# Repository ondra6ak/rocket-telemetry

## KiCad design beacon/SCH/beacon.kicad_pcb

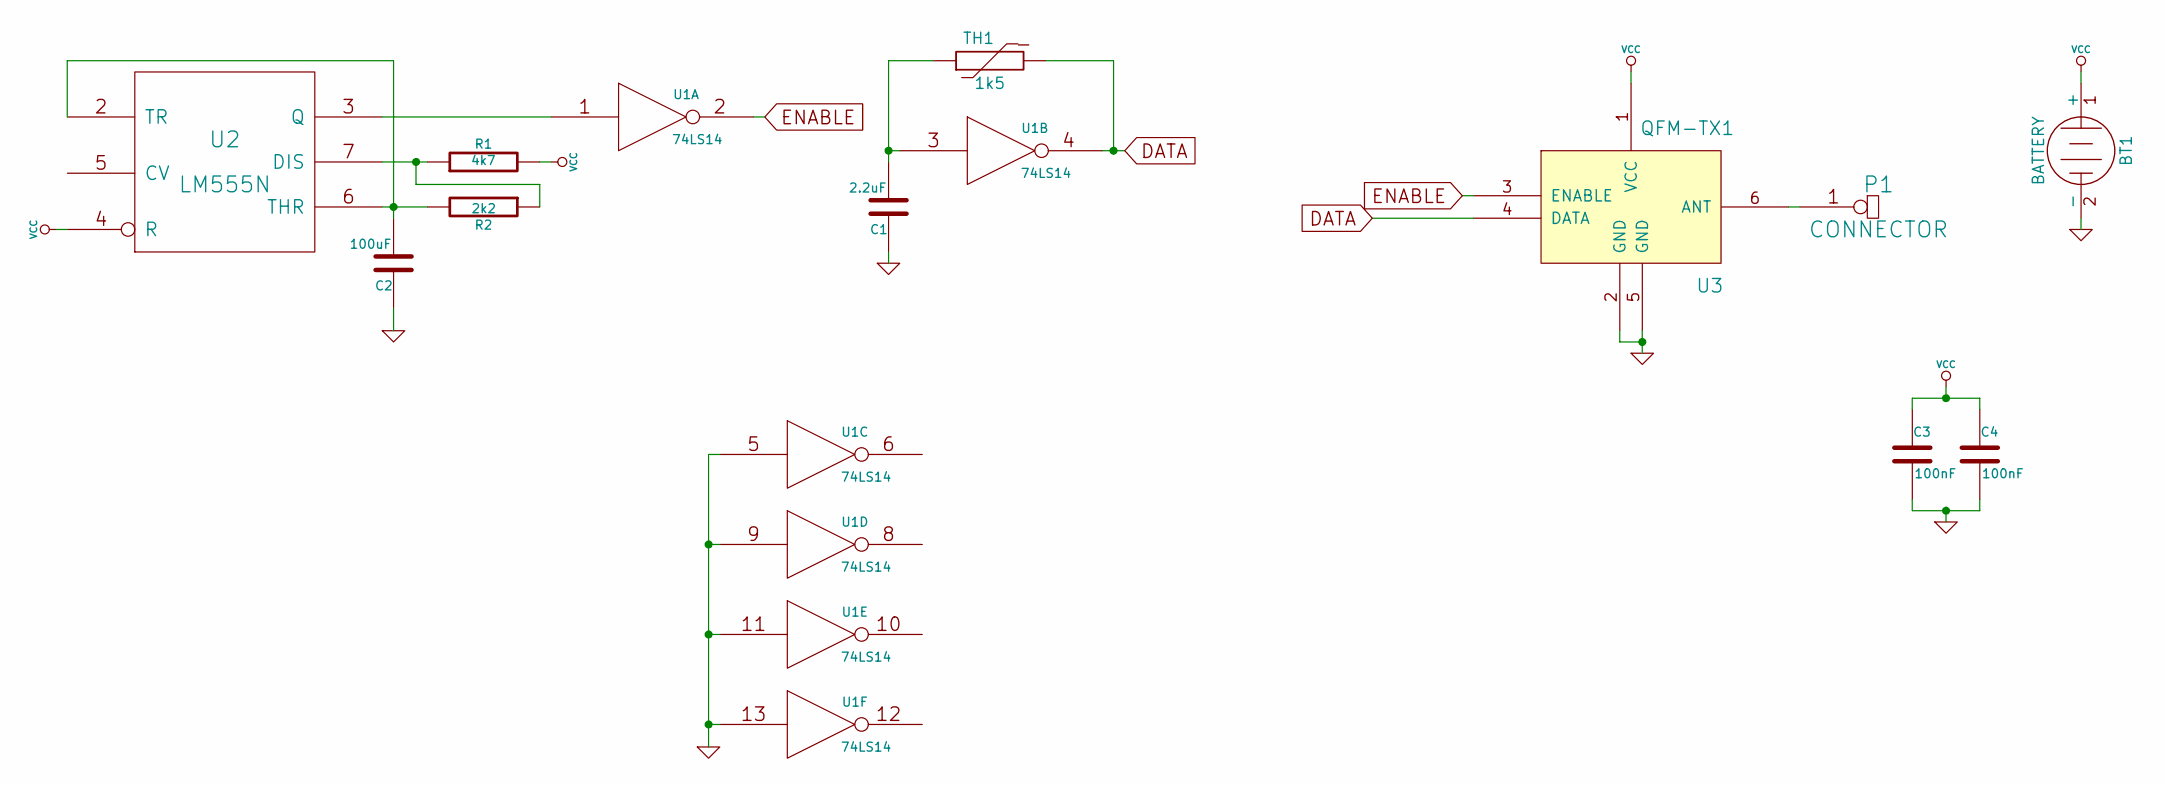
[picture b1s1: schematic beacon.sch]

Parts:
BT1: BATTERY; Coin_Cell_Holder_CH25-2032LF
C1: 2.2uF; C_0805
C2: 100uF; C_0805
C3, C4: 100nF; C_0805
P1: CONNECTOR; Pin_Header_Straight_1x01
R1: 4k7; R_0805_HandSoldering
R2: 2k2; R_0805_HandSoldering
TH1: 1k5; Capacitor7x3-5RM5_RevB
U1: 74LS14; SOIC-14_W
U2: LM555N; SOIC-8-W
U3: QFM-TX1

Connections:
DATA: TH1.2, U1.4, U3.4 (DATA)
ENABLE: U1.2, U3.3 (ENABLE)
GND: BT1.2 (-), C1.1, C2.1, C3.2, C4.2, U1.5, U1.7 (GND), U1.9, U1.11, U1.13, U2.1 (GND), U3.2 (GND), U3.5 (GND)
unnamed: C1.2, TH1.1, U1.3
unnamed: C2.2, R2.2, U2.2 (TR), U2.6 (THR)
unnamed: P1.1, U3.6 (ANT)
unnamed: R1.1, R2.1, U2.7 (DIS)
unnamed: U1.1, U2.3 (Q)
VCC: BT1.1 (+), C3.1, C4.1, R1.2, U1.14 (VCC), U2.4 (R), U2.8 (VCC), U3.1 (VCC)

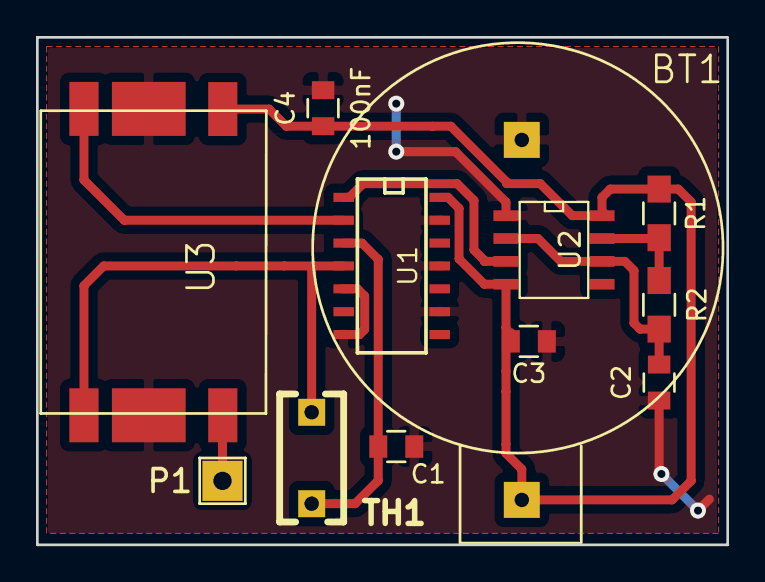
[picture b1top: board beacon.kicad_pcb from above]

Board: 2 copper layers, 38.4 x 28.2 mm, 12 parts (0 on the bottom side), 9 nets.

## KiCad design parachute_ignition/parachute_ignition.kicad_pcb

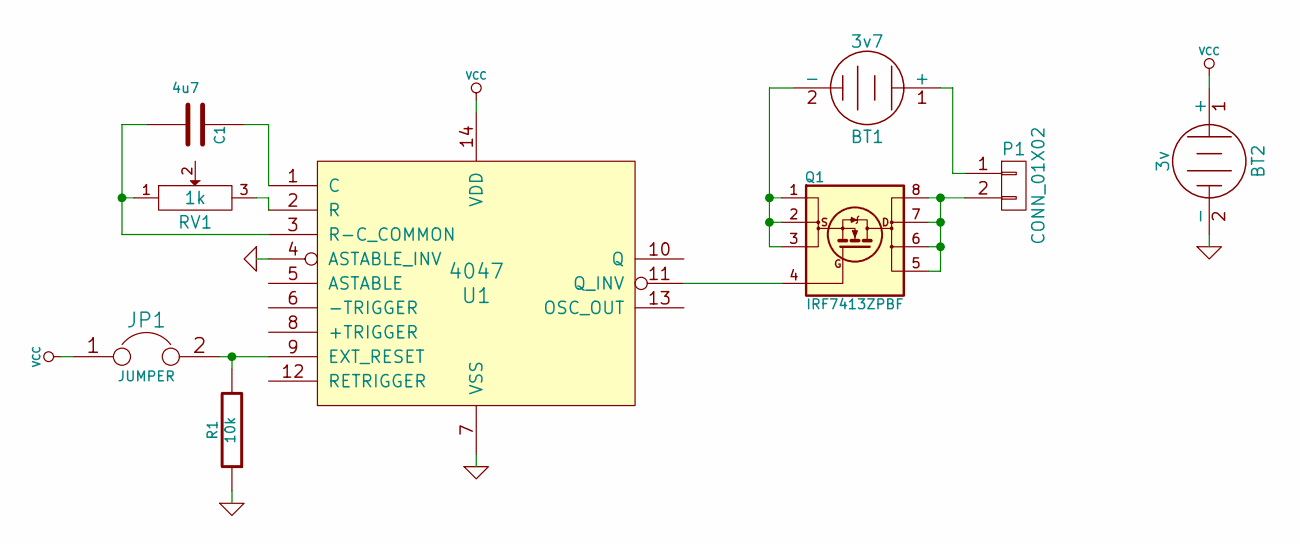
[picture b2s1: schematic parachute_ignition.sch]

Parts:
BT1: 3v7; Pin_Header_Straight_1x02
BT2: 3v; Coin_Cell_Holder_CH25-2032LF
C1: 4u7; C_0805
JP1: JUMPER; Pin_Header_Straight_1x02
P1: CONN_01X02; Pin_Header_Straight_1x02
Q1: IRF7413ZPBF; SOIC-8-W
R1: 10k; R_0805_HandSoldering
RV1: 1k; Koa_Trimmer_Smd_C
U1: 4047; SOIC-14_W

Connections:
GND: BT2.2 (-), R1.1, U1.4 (ASTABLE_INV), U1.7 (VSS)
unnamed: BT1.1 (+), P1.1
unnamed: BT1.2 (-), Q1.1 (S), Q1.2 (S), Q1.3 (S)
unnamed: C1.1, U1.1 (C)
unnamed: C1.2, RV1.1, U1.3 (R-C_COMMON)
unnamed: JP1.2, R1.2, U1.9 (EXT_RESET)
unnamed: P1.2, Q1.5 (D), Q1.6 (D), Q1.7 (D), Q1.8 (D)
unnamed: Q1.4 (G), U1.11 (Q_INV)
unnamed: RV1.3, U1.2 (R)
VCC: BT2.1 (+), JP1.1, U1.14 (VDD)

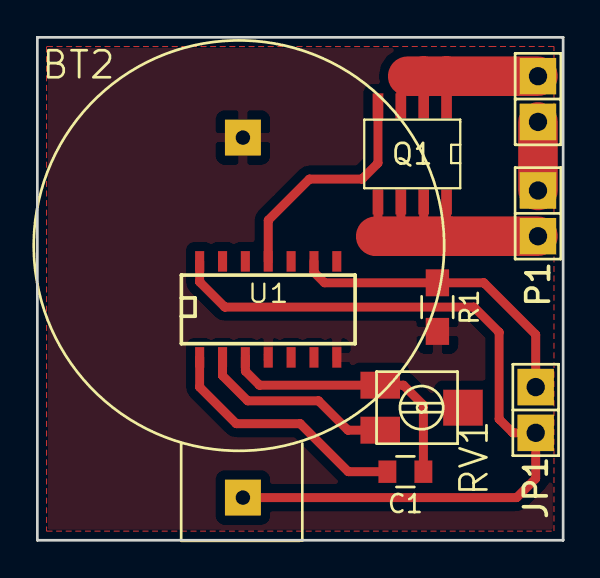
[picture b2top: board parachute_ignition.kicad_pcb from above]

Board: 2 copper layers, 29.2 x 27.9 mm, 9 parts (0 on the bottom side), 10 nets.

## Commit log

2014-09-09 transmitter added
2014-09-11 schematic cleanup
2014-09-11 capacitor value added
2014-09-14 parachute ignition circiut
2014-09-17 power on after jumper disconnection on startup
2014-09-17 ignition on for 860 ms
2014-09-18 555 and inverter replaced with 4047
2014-09-18 different hexfet
2014-09-19 emengercy quicksave
2014-09-19 prarachute ignition pcb added
2014-09-19 *-bak files are ignored
2014-09-19 transmitter pcb added
2014-09-19 jumpers reduced
2014-09-20 last improvments and pcbs
